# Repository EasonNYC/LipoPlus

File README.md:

# LiPo+ Battery Charger PCB

<div align="center">

*PCB Board Layout*

*Circuit Schematic*

</div>

A compact, single-cell LiPo battery charger PCB perfect for small electronics projects.

## Overview

LiPo+ is a battery charger PCB designed with a small form factor that can charge any single cell LiPo battery. This PCB was developed as a modular test component to validate charging functionality before integration into larger electronics projects, following a design philosophy of breaking down complex projects into smaller, testable components.

## Features

- **Universal single-cell LiPo charging** - Compatible with any single cell LiPo battery
- **Compact form factor** - Perfect for space-constrained projects
- **Mini-USB charging input** - Standard connector for easy power supply
- **Complete breakout design** with connections for:
  - Load output
  - Battery connector
  - Charging source

## Hardware Specifications

- **Charging IC**: Microchip MCP73831 LiPo Charger IC
- **Input**: Mini-USB connector
- **Battery**: Single cell LiPo (3.7V nominal)
- **Design Tool**: Cadsoft Eagle

## Design Philosophy

This PCB follows a modular design approach where complex projects are broken down into smaller, independently testable components. By validating individual subsystems like the charging circuit separately, you can:

- Reduce debugging time in final integration
- Identify issues early in the design process
- Reuse tested modules across multiple projects
- Minimize costly respins of larger, more complex PCBs

## Documentation

- **Datasheet**: [Microchip MCP73831 LiPo Charger IC](https://ww1.microchip.com/downloads/en/devicedoc/20001984g.pdf)
- **Eagle Files**: Available in this repository

## Author

Made by Eason Smith (davideasonsmith@gmail.com)

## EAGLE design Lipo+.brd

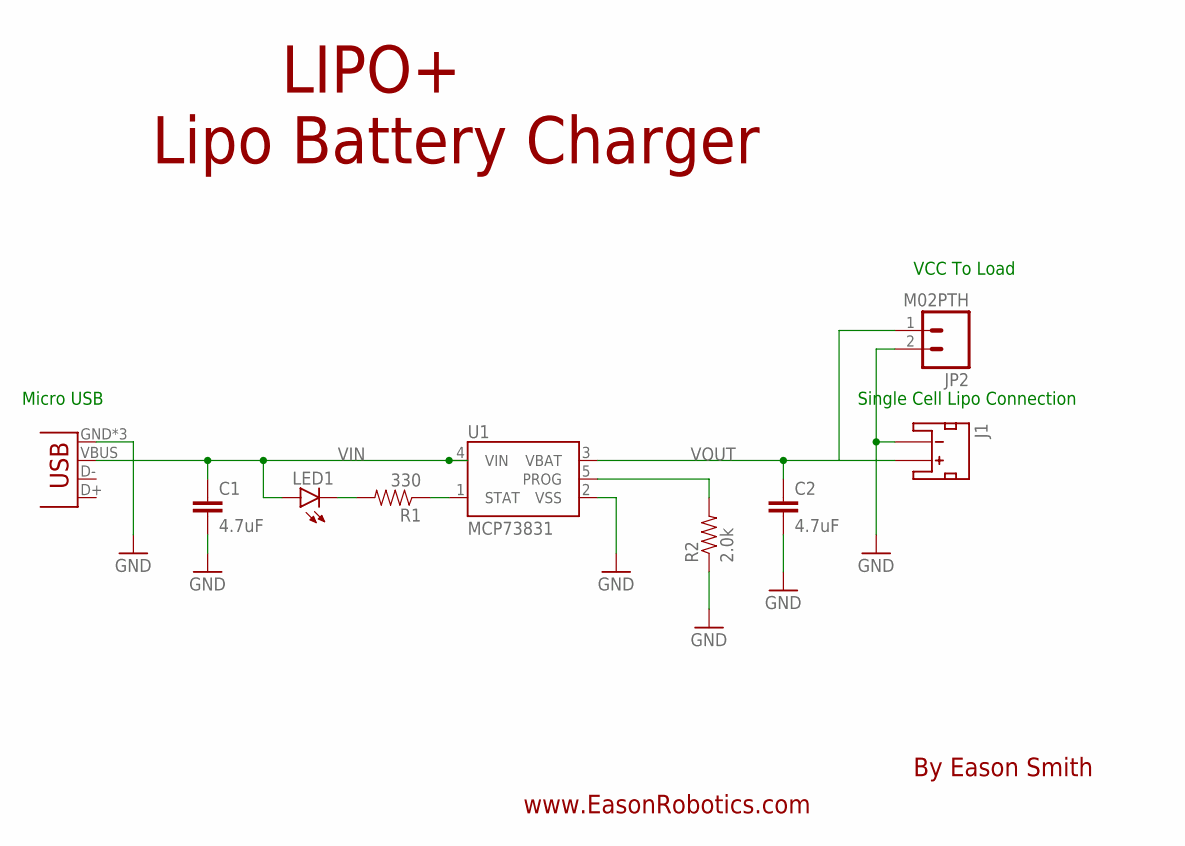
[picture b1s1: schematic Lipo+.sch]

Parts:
C1, C2: 4.7uF; 0603-CAP
J1: JST_2MM_MALE; JST-2-SMD
JP1: USB-MICROB
JP2: M02PTH; 1X02
LED1: LED0603; LED-0603
R1: 330; 0603-RES
R2: 2.0k; 0603-RES
U1: MCP73831; SOT23-5

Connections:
GND: C1.2, C2.2, J1.1 (-), JP1.GND, JP1.MT1 (GND), JP1.MT2 (GND), JP2.2, R2.1, U1.2 (VSS)
unnamed: R1.1, U1.1 (STAT)
unnamed: LED1.C, R1.2
unnamed: R2.2, U1.5 (PROG)
VIN: C1.1, JP1.VBUS, LED1.A, U1.4 (VIN)
VOUT: C2.1, J1.2 (+), JP2.1, U1.3 (VBAT)

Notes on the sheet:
Single Cell Lipo Connection
Micro USB
VCC To Load
By Eason Smith
www.EasonRobotics.com
LIPO+ Lipo Battery Charger

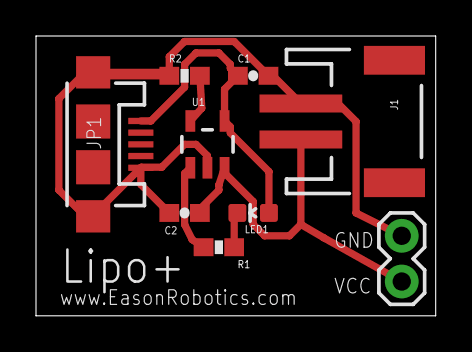
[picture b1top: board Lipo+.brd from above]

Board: 2 copper layers, 22.2 x 15.5 mm, 9 parts (0 on the bottom side), 6 nets.

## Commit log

2025-08-09 added lipo plus images and better readme
2025-08-09 fixed board image
2025-08-09 updated email address

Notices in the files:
parts and their libraries:
SparkFun-PowerIC: Licensing: Creative Commons ShareAlike 4.0 International - https://creativecommons.org/licenses/by-sa/4.0
